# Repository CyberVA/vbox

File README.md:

# VBox: Low profile hitbox-layout fightstick

This repository is a fork of jfedor2's Flatbox project. Their original files are located in this repo [here](jfedor2_files).
You can also check our their repository [here](https://github.com/jfedor2/flatbox)

Changes from the original flatbox_rev4:
- Added RGB.
- Added OLED
- Relocated RP2040 and other various components for cosmetic reasons.

## PCB Image:

## Schematic Images:

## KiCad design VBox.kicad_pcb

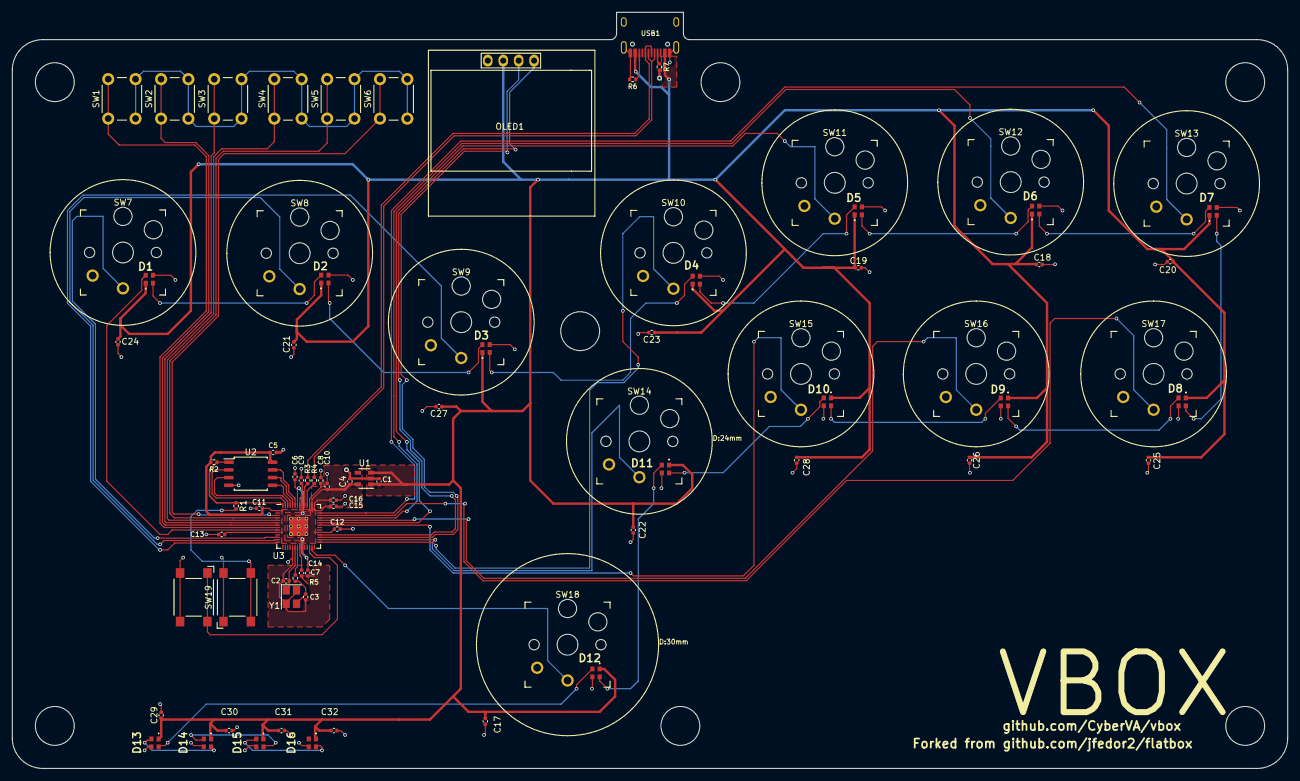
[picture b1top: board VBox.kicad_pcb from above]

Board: 2 copper layers, 210.0 x 124.5 mm, 88 parts (0 on the bottom side), 57 nets.

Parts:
C1, C4, C8, C10: 1uF; C_0402_1005Metric
C2, C3: 30pF; C_0402_1005Metric
C5, C6, C7, C9, C11, C12, C13, C14, C15, C16, C17, C18, C19, C20, C21, C22, C23, C24, C25, C26, C27, C28, C29, C30, C31, C32: 100nF; C_0402_1005Metric
D1, D2, D3, D4, D5, D6, D7, D8, D9, D10, D11, D12, D13, D14, D15, D16: SK6812-EC20; SK6812EC20
H1, H2, H3, H4, H5, H6, H7: MountingHole; MountingHole_6.4mm_M6
OLED1: SSD1306; 128x64OLED
R1, R5: 1k; R_0402_1005Metric
R2: 10k; R_0402_1005Metric
R3, R4: 27; R_0402_1005Metric
R6, R7: 5.1k; R_0402_1005Metric
SW1, SW2, SW3, SW4, SW5, SW6: SW_Push; SW_PUSH_6mm_H5mm
SW7, SW8, SW9, SW10, SW11, SW12, SW13, SW14, SW15, SW16, SW17, SW18: SW_Push; Kailh_socket_PG1350_optional
SW19, SW20: SW_Push; SW_SPST_Omron_B3FS-100xP
U1: TLV73333PDBV; SOT-23-5
U2: W25Q128JVS; SOIC-8_5.23x5.23mm_P1.27mm
U3: RP2040; RP2040-QFN-56
USB1: HRO-TYPE-C-31-M-12; HRO-TYPE-C-31-M-12-Assembly
Y1: Crystal_GND24; Crystal_SMD_3225-4Pin_3.2x2.5mm

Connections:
+1V1: C6.1, C7.1, C8.1, U3.23 (DVDD), U3.45 (VREG_VOUT), U3.50 (DVDD)
+3V3: C4.1, C5.1, C9.1, C10.1, C11.1, C12.1, C13.1, C14.1, C15.1, C16.1, R2.2, U1.5 (OUT), U2.8 (VCC), U3.1 (IOVDD), U3.10 (IOVDD), U3.22 (IOVDD), U3.33 (IOVDD), U3.42 (IOVDD), U3.43 (ADC_AVDD), U3.44 (VREG_IN), U3.48 (USB_VDD), U3.49 (IOVDD)
+5V: C1.1, C17.1, C18.1, C19.1, C20.1, C21.1, C22.1, C23.1, C24.1, C25.1, C26.1, C27.1, C28.1, C29.1, C30.1, C31.1, C32.1, D1.1 (VDD), D2.1 (VDD), D3.1 (VDD), D4.1 (VDD), D5.1 (VDD), D6.1 (VDD), D7.1 (VDD), D8.1 (VDD), D9.1 (VDD), D10.1 (VDD), D11.1 (VDD), D12.1 (VDD), D13.1 (VDD), D14.1 (VDD), D15.1 (VDD), D16.1 (VDD), OLED1.2 (VCC), U1.1 (IN), U1.3 (EN), USB1.2 (VBUS), USB1.11 (VBUS)
CIRCLE: SW15.1, U3.36 (GPIO24)
CROSS: SW14.1, U3.30 (GPIO19)
DOWN: SW8.1, U3.13 (GPIO10)
GND: C1.2, C2.2, C3.2, C4.2, C5.2, C6.2, C7.2, C8.2, C9.2, C10.2, C11.2, C12.2, C13.2, C14.2, C15.2, C16.2, C17.2, C18.2, C19.2, C20.2, C21.2, C22.2, C23.2, C24.2, C25.2, C26.2, C27.2, C28.2, C29.2, C30.2, C31.2, C32.2, D1.3 (GND), D2.3 (GND), D3.3 (GND), D4.3 (GND), D5.3 (GND), D6.3 (GND), D7.3 (GND), D8.3 (GND), D9.3 (GND), D10.3 (GND), D11.3 (GND), D12.3 (GND), D13.3 (GND), D14.3 (GND), D15.3 (GND), D16.3 (GND), OLED1.1 (GND), R6.2, R7.2, SW1.2, SW2.2, SW3.2, SW4.2, SW5.2, SW6.2, SW7.2, SW8.2, SW9.2, SW10.2, SW11.2, SW12.2, SW13.2, SW14.2, SW15.2, SW16.2, SW17.2, SW18.2, SW19.2, SW20.1, U1.2 (GND), U2.4 (GND), U3.19 (TESTEN), U3.57 (GND), USB1.1 (GND), USB1.12 (GND), USB1.13 (SHIELD), Y1.2, Y1.4
L1: SW13.1, U3.41 (GPIO29_ADC3)
L2: SW17.1, U3.40 (GPIO28_ADC2)
LEFT: SW7.1, U3.12 (GPIO9)
unnamed: C3.1, R5.2, Y1.3
unnamed: R1.2, SW19.1
unnamed: SW20.2, U3.26 (RUN)
unnamed: R4.1, U3.46 (USB_DM)
unnamed: R3.1, U3.47 (USB_DP)
unnamed: R7.1, USB1.4 (CC1)
unnamed: R6.1, USB1.10 (CC2)
OPT1: SW1.1, U3.8 (GPIO6)
OPT2: SW2.1, U3.7 (GPIO5)
OPT3: SW3.1, U3.6 (GPIO4)
OPT4: SW4.1, U3.5 (GPIO3)
OPT5: SW5.1, U3.4 (GPIO2)
OPT6: SW6.1, U3.3 (GPIO1)
QSPI_SCLK: U2.6 (CLK), U3.52 (QSPI_SCLK)
QSPI_SD0: U2.5 (DI(IO0)), U3.53 (QSPI_SD0)
QSPI_SD1: U2.2 (DO(IO1)), U3.55 (QSPI_SD1)
QSPI_SD2: U2.3 (IO2), U3.54 (QSPI_SD2)
QSPI_SD3: U2.7 (IO3), U3.51 (QSPI_SD3)
QSPI_SS: R1.1, R2.1, U2.1 (~CS), U3.56 (QSPI_SS)
R1: SW12.1, U3.39 (GPIO27_ADC1)
R2: SW16.1, U3.38 (GPIO26_ADC0)
RGB_DATA_CIRCLE: D9.2 (DOUT), D10.4 (DIN)
RGB_DATA_CROSS: D10.2 (DOUT), D11.4 (DIN)
RGB_DATA_DOWN: D1.2 (DOUT), D2.4 (DIN)
RGB_DATA_L1: D6.2 (DOUT), D7.4 (DIN)
RGB_DATA_L2: D7.2 (DOUT), D8.4 (DIN)
RGB_DATA_LEFT: D1.4 (DIN), U3.9 (GPIO7)
RGB_DATA_P1: D12.2 (DOUT), D13.4 (DIN)
RGB_DATA_P2: D13.2 (DOUT), D14.4 (DIN)
RGB_DATA_P3: D14.2 (DOUT), D15.4 (DIN)
RGB_DATA_P4: D15.2 (DOUT), D16.4 (DIN)
RGB_DATA_R1: D5.2 (DOUT), D6.4 (DIN)
RGB_DATA_R2: D8.2 (DOUT), D9.4 (DIN)
RGB_DATA_RIGHT: D2.2 (DOUT), D3.4 (DIN)
RGB_DATA_SQUARE: D3.2 (DOUT), D4.4 (DIN)
RGB_DATA_TRIANGLE: D4.2 (DOUT), D5.4 (DIN)
RGB_DATA_UP: D11.2 (DOUT), D12.4 (DIN)
RIGHT: SW9.1, U3.14 (GPIO11)
SCL: OLED1.3 (SCL), U3.31 (GPIO20)
SDA: OLED1.4 (SDA), U3.32 (GPIO21)
SQUARE: SW10.1, U3.29 (GPIO18)
TRIANGLE: SW11.1, U3.37 (GPIO25)
UP: SW18.1, U3.27 (GPIO16)
USB_D+: R3.2, USB1.6 (DP1), USB1.8 (DP2)
USB_D-: R4.2, USB1.5 (DN2), USB1.7 (DN1)
XIN: C2.1, U3.20 (XIN), Y1.1
XOUT: R5.1, U3.21 (XOUT)

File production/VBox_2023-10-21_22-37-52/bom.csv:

Designator,Footprint,Quantity,Value,LCSC Part #
"C1, C10, C4, C8",0402,4,1u,
"C11, C12, C13, C14, C15, C16, C5, C6, C7, C9",0402,10,100n,
"C17, C18, C19, C20, C21, C22, C23, C24, C25, C26, C27, C28, C29, C30, C31, C32",0402,16,100nF,C52923
"C2, C3",0402,2,30p,
"D1, D10, D11, D12, D13, D14, D15, D16, D2, D3, D4, D5, D6, D7, D8, D9",SK6812EC20,16,SK6812-EC20,
"H1, H2, H3, H4, H5, H6, H7",MountingHole_6.4mm_M6,7,MountingHole,
OLED1,128x64OLED,1,SSD1306,
"R1, R5",0402,2,1k,
R2,0402,1,10k,
"R3, R4",0402,2,27,
"R6, R7",0402,2,5.1k,
"SW1, SW2, SW3, SW4, SW5, SW6",SW_PUSH_6mm_H5mm,6,SW_Push,
"SW10, SW11, SW12, SW13, SW14, SW15, SW16, SW17, SW18, SW7, SW8, SW9",Kailh_socket_PG1350_optional,12,SW_Push,
"SW19, SW20",SW_SPST_Omron_B3FS-100xP,2,SW_Push,
U1,SOT-23-5,1,TLV73333PDBV,
U2,SOIC-8_5.23x5.23mm_P1.27mm,1,W25Q128JVS,
U3,RP2040-QFN-56,1,RP2040,
USB1,HRO-TYPE-C-31-M-12-Assembly,1,HRO-TYPE-C-31-M-12,
Y1,Crystal_SMD_3225-4Pin_3.2x2.5mm,1,Crystal_GND24,

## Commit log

2023-10-21 Reorganization and addition of my own files
2023-10-21 text
2023-10-23 Production files, Gerbers, and adjustments
